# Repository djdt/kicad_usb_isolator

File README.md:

## USB isolator ##

Board is available at https://oshpark.com/shared_projects/zpJ1wBs0

| Part No. | Value |
| ------------ | --------|
| U1           | ADUM4160 |
| U2 | CRE1S0505S3C |
| R1-4        | 24R    |
| C1-4        | 0u1    |
| C5           | 1u       |
| C6           | 10u     |
| L1,2,4,5  | Ferrite Bead |
| L3            | 10u (Panasonic G)    |

*R9 and D1 are only needed if indicator required*

*Bridge both FS **or** both LS pads with solder / 0R 0402 to set full or low speed modes*

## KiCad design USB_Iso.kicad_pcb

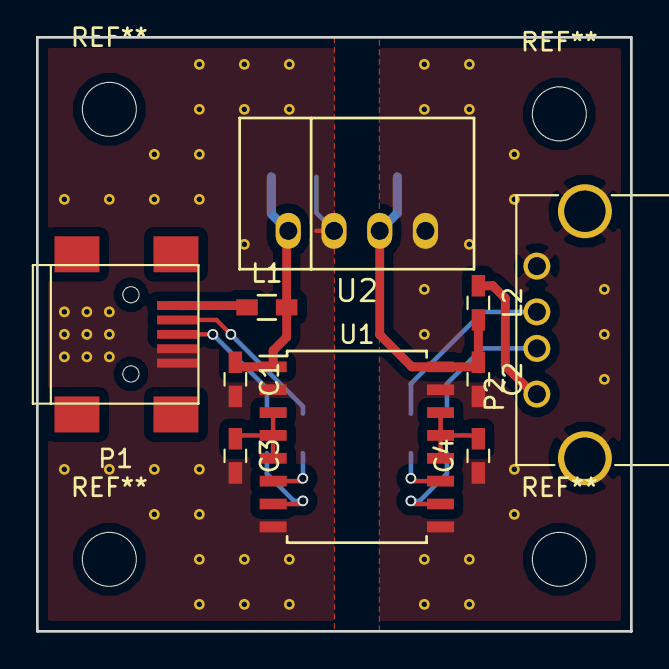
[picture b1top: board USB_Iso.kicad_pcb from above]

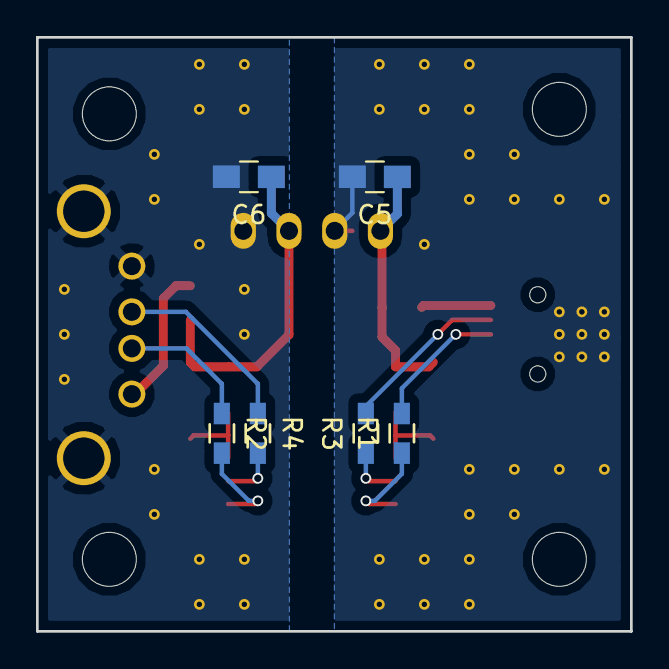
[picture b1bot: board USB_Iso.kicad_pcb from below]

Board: 2 copper layers, 33.0 x 33.0 mm, 16 parts (6 on the bottom side), 16 nets.

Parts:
C1, C2, C3, C4: 0u1; C_0603_HandSoldering
C5, C6: 10u; C_0805_HandSoldering
L1: Ferrite_Bead_Small; R_0603_HandSoldering
L2: Ferrite_Bead_Small; C_0603_HandSoldering
P1: USB_B; USB_Mini-B
P2: USB_A
R1, R2, R3, R4: 22; R_0603_HandSoldering
U1: ADUM4160; SOIC-16W_7.5x10.3mm_Pitch1.27mm
U2: CRE1

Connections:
+5V: C2.1, C6.1, L2.2, U1.16, U2.3
GND: C1.2, C3.2, C5.2, P1.4, P1.5, U1.2, U1.8, U2.2
GNDA: C2.2, C4.1, C6.2, P2.4, P2.5, U1.9, U1.15, U2.4
unnamed: C3.1, U1.3, U1.4, U1.5
unnamed: C4.2, U1.12, U1.13, U1.14
unnamed: L1.1, P1.1
unnamed: L2.1, P2.1
unnamed: P1.2, R3.2
unnamed: P1.3, R1.2
unnamed: P2.2, R2.1
unnamed: P2.3, R4.1
unnamed: R1.1, U1.7
unnamed: R2.2, U1.10
unnamed: R3.1, U1.6
unnamed: R4.2, U1.11
VCC: C1.1, C5.1, L1.2, U1.1, U2.1

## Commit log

2018-05-13 Initial
